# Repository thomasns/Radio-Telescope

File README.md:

# Radio-Telescope
Software and Hardware created for restoring the ETSU Radio Telescope

http://thomasns.io/srt.html

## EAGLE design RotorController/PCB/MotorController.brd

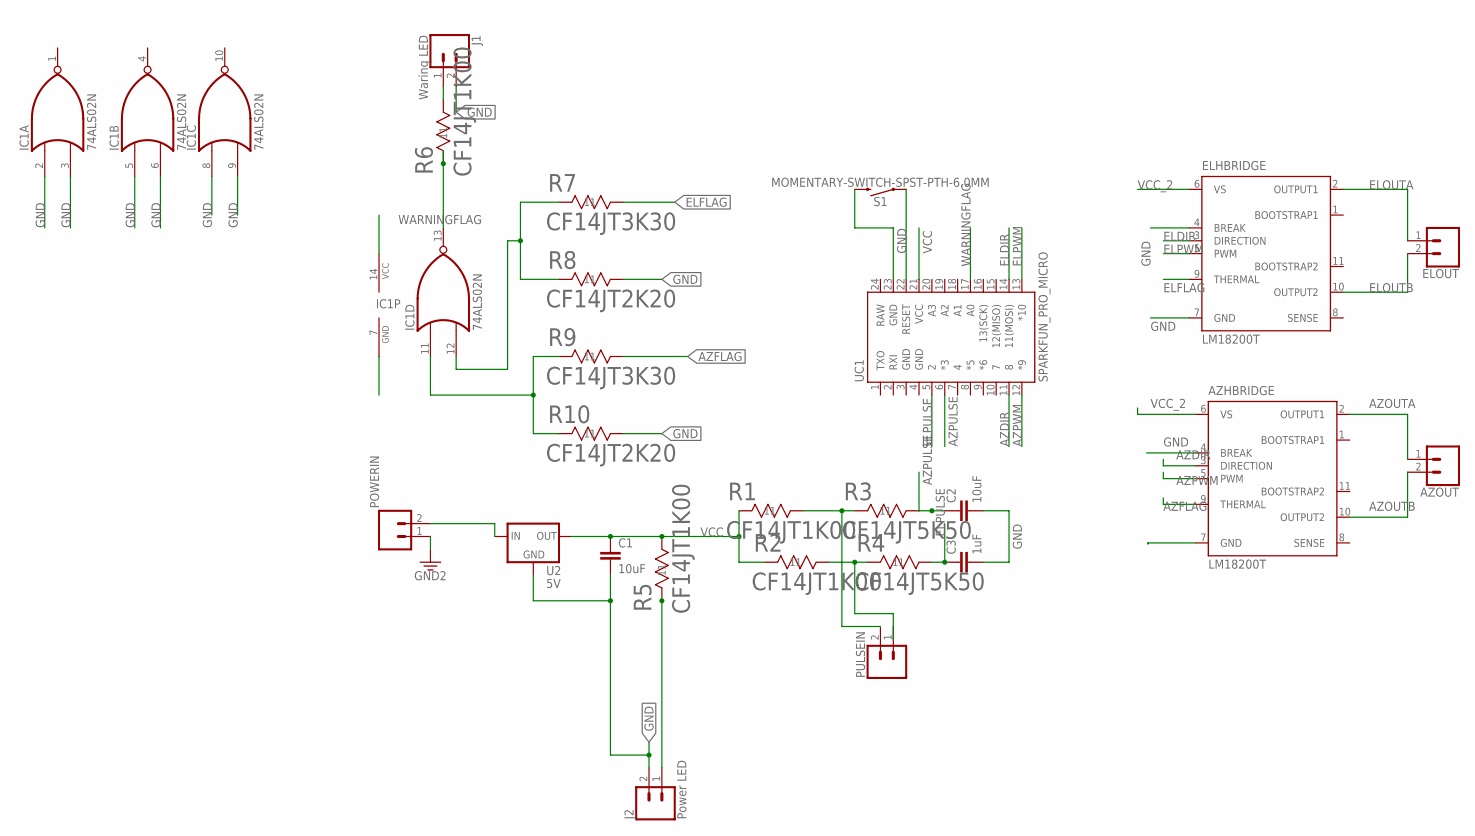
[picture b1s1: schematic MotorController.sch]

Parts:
AZHBRIDGE: LM18200T; TO-220-11
AZOUT: CONN_02; 1X02
C1, C2: 10uF; CAP-PTH-SMALL-KIT
C3: 1uF; CAP-PTH-SMALL-KIT
ELHBRIDGE: LM18200T; TO-220-11
ELOUT: CONN_02; 1X02
IC1: 74ALS02N; DIL14
J1: Waring LED; 1X02
J2: Power LED; 1X02
POWERIN: CONN_02; 1X02
PULSEIN: CONN_02; 1X02
R1, R2, R5, R6: CF14JT1K00; STA_CF14
R3, R4: CF14JT5K50; STA_CF14
R7, R9: CF14JT3K30; STA_CF14
R8, R10: CF14JT2K20; STA_CF14
S1: MOMENTARY-SWITCH-SPST-PTH-6.0MM; TACTILE_SWITCH_PTH_6.0MM
U2: 5V; TO220-IGO
UC1: SPARKFUN_PRO_MICRO

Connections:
AZDIR: AZHBRIDGE.3 (DIRECTION), UC1.11 (8)
AZFLAG: AZHBRIDGE.9 (THERMAL), R9.2 (22)
AZOUTA: AZHBRIDGE.2 (OUTPUT1), AZOUT.1
AZOUTB: AZHBRIDGE.10 (OUTPUT2), AZOUT.2
AZPULSE: C2.1, R3.2 (22), UC1.6 (*3)
AZPWM: AZHBRIDGE.5 (PWM), UC1.12 (*9)
ELDIR: ELHBRIDGE.3 (DIRECTION), UC1.14 (11(MOSI))
ELFLAG: ELHBRIDGE.9 (THERMAL), R7.2 (22)
ELOUTA: ELHBRIDGE.2 (OUTPUT1), ELOUT.1
ELOUTB: ELHBRIDGE.10 (OUTPUT2), ELOUT.2
ELPULSE: C3.1, R4.2 (22), UC1.5 (2)
ELPWM: ELHBRIDGE.5 (PWM), UC1.13 (*10)
GND: AZHBRIDGE.4 (BREAK), AZHBRIDGE.7 (GND), C1.2, C2.2, C3.2, ELHBRIDGE.4 (BREAK), ELHBRIDGE.7 (GND), IC1.2 (I0), IC1.3 (I1), IC1.5 (I0), IC1.6 (I1), IC1.7 (GND), IC1.8 (I0), IC1.9 (I1), J1.2, J2.2, POWERIN.1, R8.2 (22), R10.2 (22), S1.3 (2), U2.GND, UC1.3 (GND), UC1.4 (GND), UC1.23 (GND)
unnamed: S1.1, UC1.22 (RESET)
unnamed: PULSEIN.2, R1.2 (22), R3.1 (11)
unnamed: IC1.12 (I1), R7.1 (11), R8.1 (11)
unnamed: PULSEIN.1, R2.2 (22), R4.1 (11)
unnamed: J1.1, R6.2 (22)
unnamed: J2.1, R5.1 (11)
unnamed: IC1.11 (I0), R9.1 (11), R10.1 (11)
RAW: UC1.24 (RAW)
VCC: C1.1, IC1.14 (VCC), R1.1 (11), R2.1 (11), R5.2 (22), U2.OUT, UC1.21 (VCC)
VCC_2: AZHBRIDGE.6 (VS), ELHBRIDGE.6 (VS), POWERIN.2, U2.IN
WARNINGFLAG: IC1.13 (O), R6.1 (11), UC1.17 (A0)

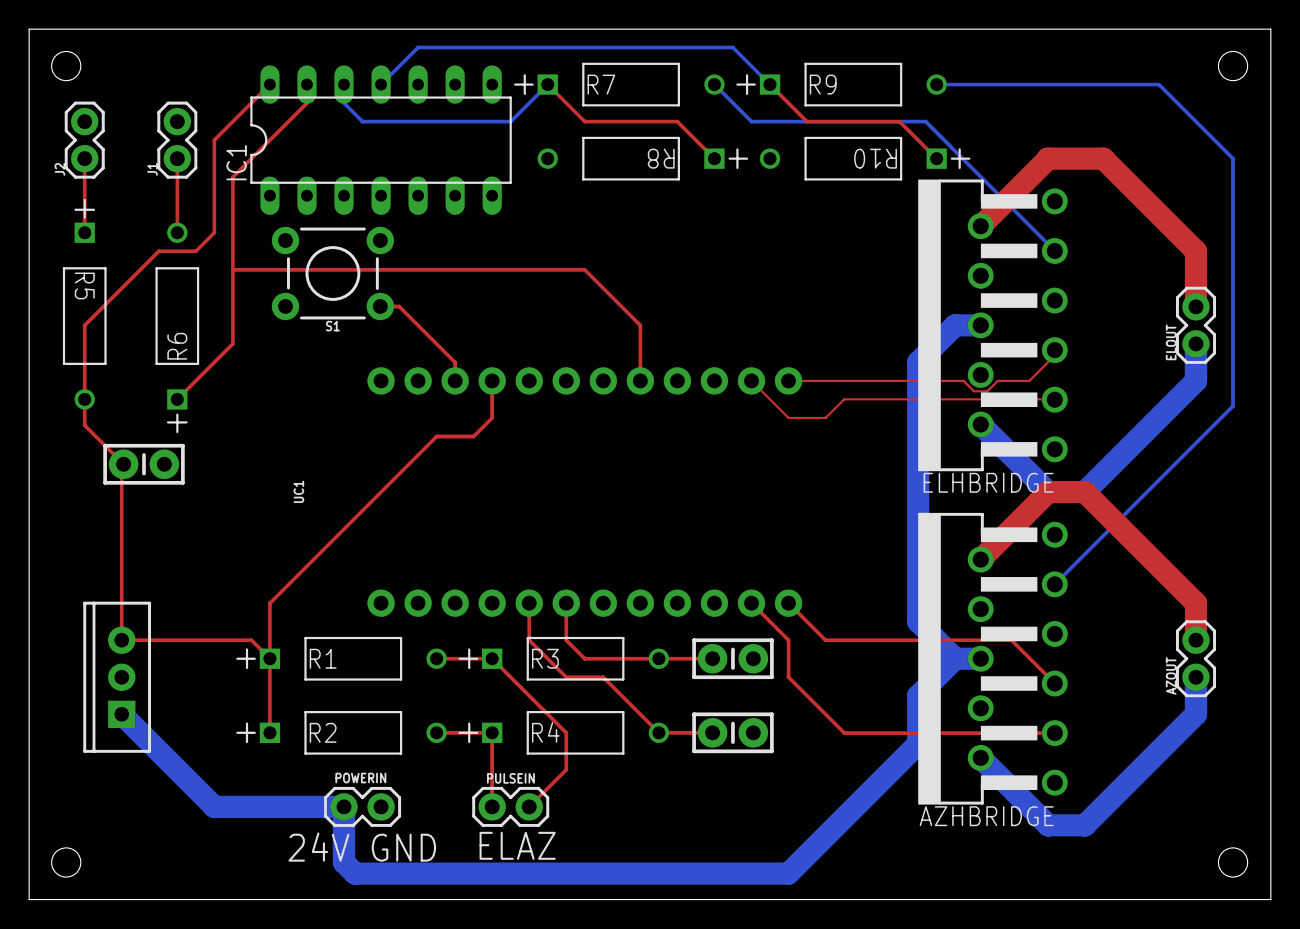
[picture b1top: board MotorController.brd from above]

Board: 2 copper layers, 85.1 x 59.7 mm, 25 parts (0 on the bottom side), 23 nets.

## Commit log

2018-10-18 Add existing files
2018-10-20 Added initial PCB files
2018-10-26 Added thermal warning logic and fixed some layout issues.
2019-01-05 Fixed PCB files with accurate footprints for passive components. Included gerber files. Updated the arduino project layout.
2019-01-05 Added bill of materials
2019-01-17 Added a basic python script to control the motor controller. This is just an abstraction at this point no real serial interfacing.
2019-01-23 Started adding serial communication to the motor controller. Known bugs: only sends the first move command currently. Ocassionally sents a malformed command to the arduino, causing a reset
2019-01-24 Fixed issue with only one command sending. Forgot to add \n to command strings
2019-01-24 Updated BOM. Incorrect part number for the or gate.
2019-08-11 Cleaned controller class. Added documentation folder with rough class diagram.
2019-08-11 Actually added documentation directory Botched the last commit
2019-08-12 Initial tracking code
    Added new tracking class and updated driver code to test it.
    Not 100% but some progress.
    Added docstrings to RotorController class.
    Updated class diagram.
2019-08-12 Botched last commit, pushing updated class diagram, controller.py and new test driver
2019-08-13 More work with the tracking Found and fixed multiple bugs in the rotorController class. Renamed RA/DEC to AZ/ALT
2019-08-15 Updated class diagram to match changes from RA/EL to ALT/AZ Cleaned pdf output

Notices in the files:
parts and their libraries:
SparkFun-Connectors: Licensing: Creative Commons ShareAlike 4.0 International - https://creativecommons.org/licenses/by-sa/4.0
